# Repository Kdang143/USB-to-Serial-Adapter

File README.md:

# USB-to-Serial-Adapter
Designed to allow USB ports to be converted into Serial ports for Ryerson's Robotics Club Rover.

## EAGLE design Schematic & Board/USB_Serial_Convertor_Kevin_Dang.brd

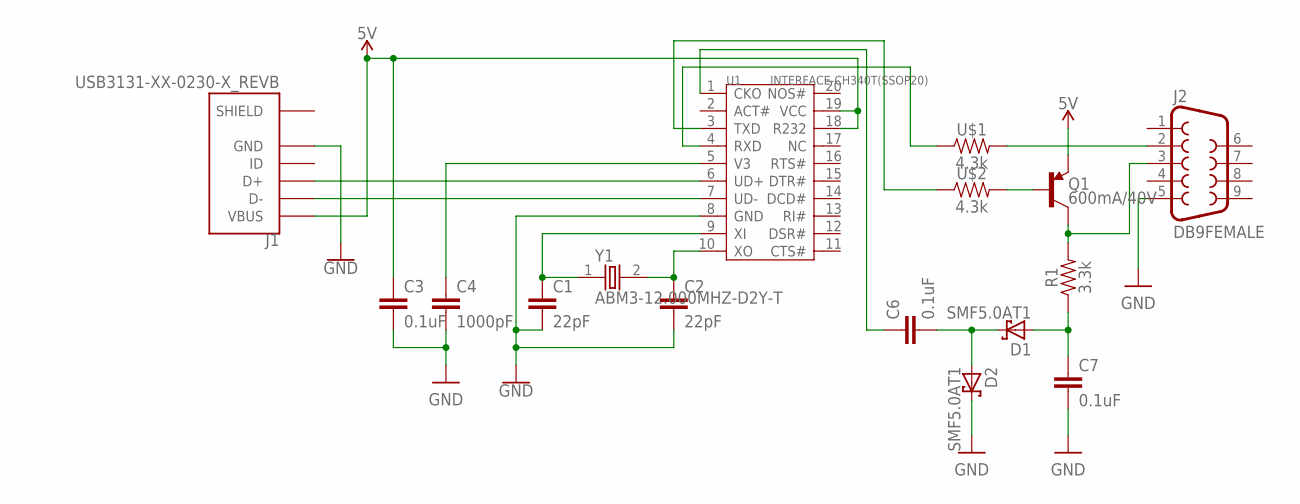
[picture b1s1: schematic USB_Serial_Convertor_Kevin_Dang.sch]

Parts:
C1, C2: 22pF; 0402-TIGHT
C3, C6, C7: 0.1uF; 0402-TIGHT
C4: 1000pF; 0402-TIGHT
D1, D2: SMF5.0AT1; SOD123FL
J1: USB3131-XX-0230-X_REVB; GCT_USB3131-XX-0230-X_REVB
J2: DB9FEMALE; DB9
Q1: 600mA/40V; SOT23-3
R1: 3.3k; 0603
U1: INTERFACE-CH340T(SSOP20); SSOP20-0.65-7.6X5.2MM
U$1, U$2: 4.3k; 0402_MURATA
Y1: ABM3-12.000MHZ-D2Y-T; XTAL500X320X130N

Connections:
5V: C3.1, J1.1 (VBUS), Q1.2 (E), U1.18 (R232), U1.19 (VCC)
GND: C1.2, C2.2, C3.2, C4.2, C7.2, D2.C, J1.5 (GND), J2.5, U1.8 (GND)
unnamed: J1.3 (D+), U1.6 (UD+)
unnamed: J1.2 (D-), U1.7 (UD-)
unnamed: C1.1, U1.9 (XI), Y1.1
unnamed: C2.1, U1.10 (XO), Y1.2
unnamed: U1.4 (RXD), U$1.P$1 (1)
unnamed: J2.2, U$1.P$2 (2)
unnamed: U1.3 (TXD), U$2.P$1 (1)
unnamed: Q1.1 (B), U$2.P$2 (2)
unnamed: J2.3, Q1.3 (C), R1.2
unnamed: C7.1, D1.A, R1.1
unnamed: C6.2, D1.C, D2.A
unnamed: C6.1, U1.1 (CKO)
V3: C4.1, U1.5 (V3)

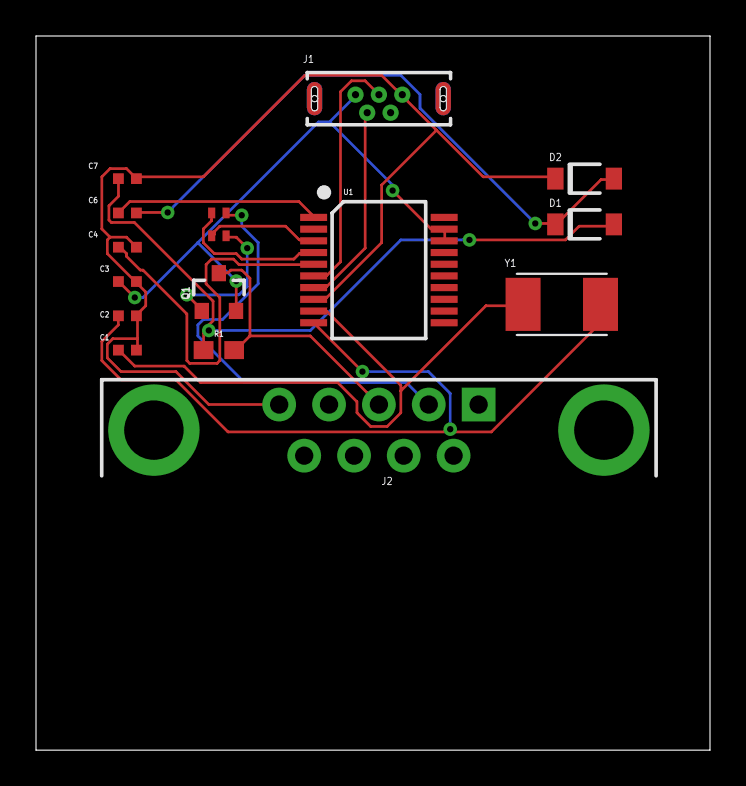
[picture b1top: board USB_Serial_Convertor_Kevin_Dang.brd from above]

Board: 2 copper layers, 37.4 x 39.7 mm, 16 parts (0 on the bottom side), 15 nets.

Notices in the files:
parts and their libraries:
SparkFun-Capacitors: Licensing: Creative Commons ShareAlike 4.0 International - https://creativecommons.org/licenses/by-sa/4.0
